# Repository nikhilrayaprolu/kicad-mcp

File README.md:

# kicad-mcp

**An MCP server that lets an AI agent design real, manufacturable PCBs.** The agent decides what a human electronics engineer decides: parts, connections, reference circuits, design rules, floorplan, and which parts must sit close to which pins. Deterministic engines turn that intent into a KiCad 10 project:

- a hierarchical schematic
- double-sided placement
- human-like routing with coupled differential pairs and length tuning
- copper pours
- DRC/ERC, Gerbers, BOM and pick-and-place

Everything runs headless.

It was built and evaluated by designing a **130-part Rockchip RV1106 Linux single-board computer from scratch** (`designs/rv1106-sbc/`):

- 4-layer, 65 × 50 mm
- USB-C, 10/100 Ethernet, SPI NAND, microSD, MIPI-CSI, 4 regulators
- **KiCad ERC 0 errors; DRC 0 errors, 0 warnings, 0 unconnected, 0 schematic-parity issues**
- every differential pair has equal via counts on both legs and is within its length tolerance (0.09–0.99 mm), using 45°-mitred serpentines
- `expert_review` quality gate: grade **expert**, 15/15 checks
- expert finishing: fiducials, labelled test points, edge via fence, legalised silkscreen

See [`docs/EVALUATION.md`](docs/EVALUATION.md).

| | |
|---|---|
| [`AGENTS.md`](AGENTS.md) | **Playbook for the AI agent**: the step-by-step flow, design rules and pitfalls that produce high-quality boards |
| [`docs/TOOLS.md`](docs/TOOLS.md) | Reference for all 28 MCP tools (generated from the server) |
| [`docs/ARCHITECTURE.md`](docs/ARCHITECTURE.md) | How it works: IR, placer, routers (own C++ router + Freerouting), verification |
| [`docs/EVALUATION.md`](docs/EVALUATION.md) | The RV1106 case study: metrics, iterations, bugs found, honest limitations |
| [`designs/rv1106-sbc/`](designs/rv1106-sbc) | Complete worked example: IR, KiCad files, every MCP call batch, fab outputs, renders |

## Gallery: the RV1106 example, generated end to end through the MCP tools

| PCB, top (3D) | PCB, bottom (3D): decoupling and crystal under the SoC |
|---|---|
|  |  |

| Layout: red F.Cu, olive In2.Cu, blue B.Cu; hatched = bottom-side parts | Length tuning: serpentine meanders on the CSI camera pairs |
|---|---|
|  |  |

| Copper pours on all 4 layers: F.Cu GND, In1 GND plane, In2 3V3/0V9/VSYS, B.Cu GND |
|---|
|  |

Generated hierarchical schematic, one sheet per functional block (ERC 0 errors, netlist identical to the design IR):

| SoC sheet: RV1106G3 symbol generated from the datasheet pin table | Power sheet: 4 bucks with E96 feedback dividers, USB-C sink, ESD |
|---|---|
|  |  |

| Ethernet sheet | Camera sheet | Root sheet |
|---|---|---|
|  |  |  |

<details><summary>v1 for comparison: single-sided, Freerouting only</summary>

| | |
|---|---|
|  |  |

</details>

---

## 1. Install (Linux x86_64, no sudo needed)

```bash
git clone git@github.com:nikhilrayaprolu/kicad-mcp.git
cd kicad-mcp
./scripts/install.sh
```

`install.sh` is idempotent and installs everything into the repo folder:

| Step | What |
|---|---|
| pixi env | Python 3.12, Java 25, `mcp`, numpy, scipy, shapely, pymupdf, … (installs pixi itself if missing) |
| KiCad 10.0.8 | `kicad-cli` and the stock symbol/footprint libraries, unpacked from the official KiCad PPA into `tools/kicad-root`, with the shared libraries it needs (tested on Ubuntu 24.04) |
| Freerouting 2.5 | `tools/freerouting/freerouting-2.5.0.jar` |
| hroute | builds the C++ router `router_cpp/hroute` (needs `g++`) |
| smoke test | `pixi run test`: 12 tests, including routed boards that must pass KiCad DRC |

If you already have **KiCad ≥ 9** (`kicad-cli` on PATH, libraries in `/usr/share/kicad`), run `SKIP_KICAD=1 ./scripts/install.sh`. On a non-Ubuntu distro, install KiCad from your package manager or Flatpak, then use `SKIP_KICAD=1`.

Hardware: any modern CPU works. Placement and routing portfolios scale with cores: 64 placement chains and 16–32 routing jobs run concurrently, about 0.4 GB RAM each. A 130-part board takes about 1–1.5 h end to end on 80 cores.

## 2. Connect it to your agent

**Claude Code:**

```bash
claude mcp add -s user kicad-mcp -- bash -c 'source /path/to/kicad-mcp/tools/env.sh && exec /path/to/kicad-mcp/.pixi/envs/default/bin/python -m llmpcb.server'
claude mcp list        # kicad-mcp: … ✔ Connected
```

**Any other MCP client** (Claude Desktop, Cursor, custom agents): it is a stdio server.

```json
{
  "mcpServers": {
    "kicad-mcp": {
      "command": "bash",
      "args": ["-c", "source /path/to/kicad-mcp/tools/env.sh && exec /path/to/kicad-mcp/.pixi/envs/default/bin/python -m llmpcb.server"]
    }
  }
}
```

Give the agent [`AGENTS.md`](AGENTS.md). In Claude Code, opening a session in this repo loads `CLAUDE.md` → `AGENTS.md`, and the `pcb-design` skill (`.claude/skills/pcb-design/`) is picked up automatically. With other agents, paste `AGENTS.md` into the system prompt or project instructions. The server also sends a condensed version as its MCP `instructions`.

**Scripted use, without an LLM client.** Run tool-call batches over real MCP stdio, which is how the example board was made:

```bash
pixi run python clients/mcp_call.py designs/myboard calls.json      # calls.json = [{"tool": ..., "args": {...}}, ...]
pixi run python clients/metrics.py designs/myboard                  # tool calls, latency, response sizes, DRC/ERC
```

## 3. How to ask for a board (for users)

The quality of the board depends mostly on the quality of your request. A good request contains:

1. **Function and interfaces:** "Linux SBC on RV1106G3 with USB-C power + USB2 device, 10/100 Ethernet (RJ45 with magnetics), SPI-NAND boot, microSD, 2-lane MIPI camera FPC, debug UART header, 2×10 GPIO header."
2. **Power:** input source and voltage, every rail with its voltage and estimated current, and sequencing if the chip needs it.
3. **Mechanics:** board size limit, connector edges, mounting holes, height limits, and whether **double-sided assembly** is allowed. That is recommended for fine-pitch SoCs: decoupling goes under the chip.
4. **Fab target:** e.g. JLCPCB 4-layer 1.6 mm (the default preset), and impedance targets for high-speed pairs.
5. **Sources:** datasheets and a reference-design schematic for every complex IC. The agent extracts pin tables into `knowledge/*.yaml` with page citations. Reference designs are the fastest way to correct support circuits.

Example prompt:

> Using the kicad-mcp server and AGENTS.md, design a 4-layer 50×40 mm ESP32-S3 board: USB-C 5 V in, 3.3 V/1 A buck, USB D+/D− to the S3 with ESD, 16 MB flash + 8 MB PSRAM (module), I2C header, 2 buttons, RGB LED, 4 M2 holes. Double-sided assembly allowed for passives. Target JLCPCB. Show me the placement render before routing, and stop only at DRC 0/0.

What you will see from the agent:

1. requirements and parts, then **schematic + ERC**
2. board setup, then **placement render**
3. **routing portfolio** (hybrid), then **DRC**
4. repair passes, then **length tuning**, then **design review**
5. **expert review**: the agent grades its own board, looks at the renders and fixes every failed check
6. **fab export + `publish`**: 3-D/2-D/per-layer/schematic images and a README gallery committed and pushed under `designs/<name>/`

You can intervene at any stage. For example: "move the USB connector to the bottom edge", "allow the crystal on the bottom side", "make VSYS 1 A", "route the camera pairs as coupled pairs".

Open the result in KiCad 10: `designs/<name>/<name>.kicad_pro`. The library tables in the project point at `llmpcb/library` for generated parts. After hand edits in KiCad, the agent can pull them back with `sync_from_kicad`.

### Quality checklist before ordering

- [ ] `expert_review` grade **expert**. It is the automated version of this list. It also checks:
  - copper pours on every layer
  - diff pairs with equal layer changes
  - 0 DRC warnings
  - stitching, fiducials, test points and labels
- [ ] `schematic_build`: ERC 0 errors, `netlist_parity.ok`
- [ ] `drc`: 0 errors, 0 unconnected, 0 parity; remaining warnings explained (pour islands, silkscreen)
- [ ] `design_review`: no errors; each `near`/`current`/`escape`/`diffpair` warning judged
- [ ] Generated footprints (`llmpcb/library`) checked against the manufacturer's land pattern
- [ ] I/O voltage domains, power sequencing and regulator choices reviewed by a human
- [ ] 3D renders (top and bottom) look right; connectors face the board edge

## 4. What is inside

| Layer | Implementation |
|---|---|
| Design IR | `design.json` (components, pin→net, netclasses, constraints, board) + `layout.json` (placement incl. side, tracks, vias, zones). KiCad files are regenerated from these. |
| Parts & knowledge | KiCad 10 stock libraries; curated parts with design facts; generated symbols/footprints from datasheet pin tables (`knowledge/*.yaml`) |
| Reference blocks | buck (E96 divider + sequencing RC), decoupling, crystal (CL→Cload), USB-C sink + ESD + pair, LED, button, … |
| Schematic | hierarchical sheets per block, labels at pin endpoints, PWR_FLAGs, ERC + netlist parity via `kicad-cli` |
| Placement | double-sided, rigid cluster macros, simulated annealing + legalisation + refinement, 64-seed parallel portfolio |
| Routing | **hroute** (own C++ router: 45°, negotiated congestion, neck-down, coupled diff pairs) + Freerouting; hybrid critical-first portfolio; DRC-scored parallel repair; serpentine length tuning |
| Verification | `kicad-cli` ERC/DRC (zones refilled, schematic parity), design review (decoupling distance, crystal, diff-pair skew and via symmetry, IPC-2221 current, escape feasibility), **`expert_review` quality gate** (pours on all layers, stitching, 45° routing, silkscreen, fiducials, test points, labels) |
| Copper | GND/power pours on every layer, saved filled; edge via fence + grid stitching; floating islands stitched to the plane (`stitch_islands`) |
| Publishing | `publish`: renders + gallery README per board, git commit/push of only that board's files |
| Output | Gerber X2, Excellon, CPL, JLC BOM, IPC-D-356, PDFs, 3D renders |

Why it writes KiCad files directly instead of using `pcbnew`/IPC: KiCad 10's IPC API needs a running GUI, and the SWIG `pcbnew` module is deprecated. kicad-cli is used as the verifier, and the writers are checked against KiCad itself. See `docs/ARCHITECTURE.md`. An optional `ipc_sync` tool pushes to or pulls from a running KiCad GUI.

## 5. Development

```bash
source tools/env.sh
pixi run test                                   # unit + end-to-end (route -> KiCad DRC clean)
pixi run python clients/gen_tool_docs.py        # regenerate docs/TOOLS.md after changing tools
g++ -O3 -march=native -std=c++17 -o router_cpp/hroute router_cpp/hroute.cpp
```

Router debugging (`router_cpp/hroute.cpp`, problem files in `designs/<x>/out/hroute/*/problem.txt`):

| Variable | Effect |
|---|---|
| `HROUTE_PROBE="net layer x y"` | ASCII legality map around a point |
| `HROUTE_DBG=1` | failed-search statistics and flood-fill reachability |
| `HROUTE_BUDGET` | negotiation time budget, in seconds |
| `HROUTE_CAP` | A* expansion cap |
| `HROUTE_SEQ=1` | legacy sequential rip-up |

## Limitations (honest)

- **hroute's completion:** it completes 75–80 of 84 nets on the dense RV1106 board; Freerouting finishes the rest in hybrid mode. Its strength is critical nets and coupled pairs.
- **Coupled pairs** survive only where the placement leaves a corridor. Others are routed single-ended and then length-tuned.
- **Generated footprints** (e.g. the QFN-128) are derived from datasheet drawings and must be verified.
- **Not covered:** high-speed DDR fan-out, impedance field solving, SI/PI/thermal simulation.
- **IPC live mode** is implemented but untested, since there was no KiCad GUI in the development environment.

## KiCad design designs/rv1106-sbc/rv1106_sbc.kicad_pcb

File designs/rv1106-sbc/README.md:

# LP-1106 RV1106 SBC (rev A)

LP-1106: Linux SBC on Rockchip RV1106G3 (Cortex-A7, 1 TOPS NPU, 256MB DDR3L in package). USB-C power+OTG, 10/100 Ethernet, SPI NAND boot, microSD, 2-lane MIPI CSI, debug UART, 2x10 GPIO.

65.0 × 50.0 mm, 4 layers, 137 parts, 374 vias. Generated with kicad-mcp.

| Check | Result |
|---|---|
| Expert review | **expert** (15 passed, 0 failed) |
| KiCad DRC | 0 errors, 0 warnings, 0 unconnected, 0 parity |
| Pour coverage | B.Cu 74%, F.Cu 57%, In1.Cu 83%, In2.Cu 62% |

| Top (3D) | Bottom (3D) |
|---|---|
|  |  |

| layer_F_Cu.png | layer_In1_Cu.png | layer_In2_Cu.png | layer_B_Cu.png |
|---|---|---|---|
|  |  |  |  |

## Schematic

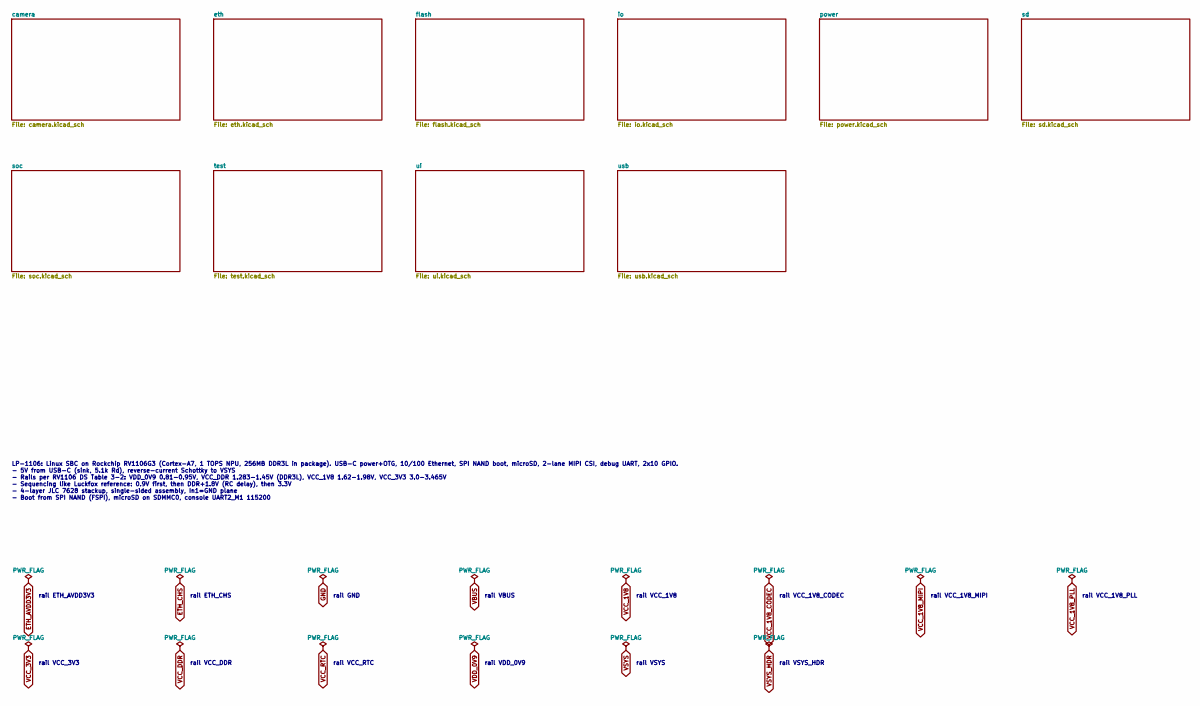
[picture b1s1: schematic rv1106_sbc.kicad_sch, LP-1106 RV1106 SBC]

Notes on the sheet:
rail ETH_AVDD3V3
rail ETH_CHS
rail GND
rail VBUS
rail VCC_1V8
rail VCC_1V8_CODEC
rail VCC_1V8_MIPI
rail VCC_1V8_PLL
rail VCC_3V3
rail VCC_DDR
rail VCC_RTC
rail VDD_0V9
rail VSYS
rail VSYS_HDR
LP-1106: Linux SBC on Rockchip RV1106G3 (Cortex-A7, 1 TOPS NPU, 256MB DDR3L in package). USB-C power+OTG, 10/100 Ethernet, SPI NAND boot, microSD, 2-lane MIPI CSI, debug UART, 2x10 GPIO. - 5V from USB-C (sink, 5.1k Rd), reverse-current Schottky to VSYS - Rails per RV1106 DS Table 3-2: VDD_0V9 0.81-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

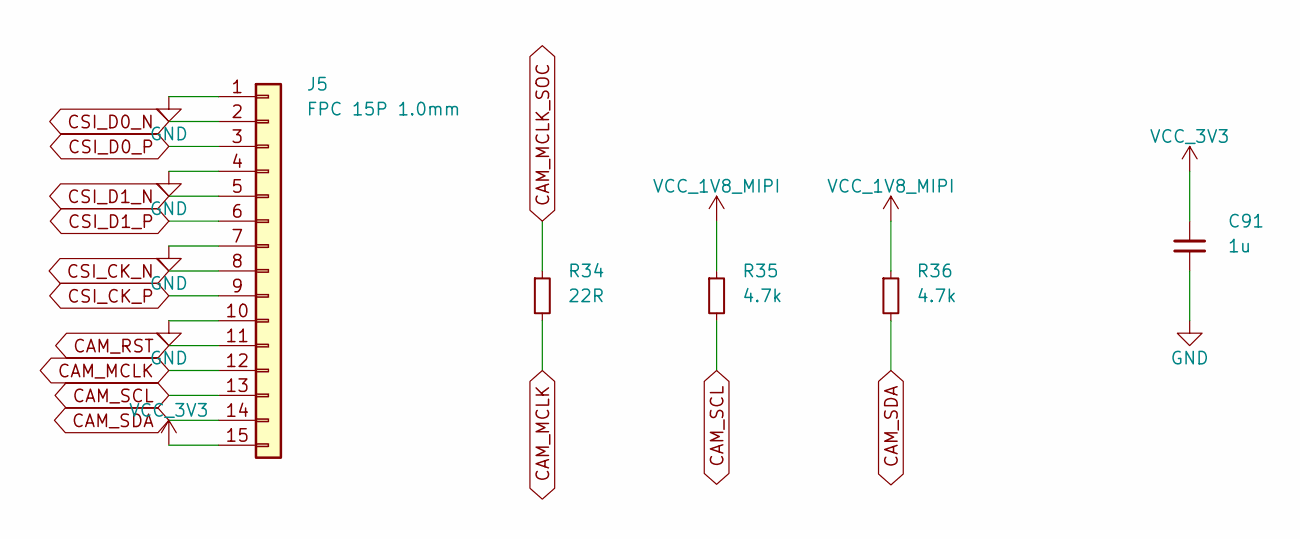
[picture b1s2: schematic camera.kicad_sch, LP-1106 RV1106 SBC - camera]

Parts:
C91: 1u; C_0402_1005Metric
J5: FPC 15P 1.0mm; Molex_200528-0150_1x15-1MP_P1.00mm_Horizontal
R34: 22R; R_0402_1005Metric
R35, R36: 4.7k; R_0402_1005Metric

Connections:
CAM_MCLK: J5.12, R34.2
CAM_MCLK_SOC: R34.1; also elsewhere on the board
CAM_RST: J5.11; also elsewhere on the board
CAM_SCL: J5.13, R35.2; also elsewhere on the board
CAM_SDA: J5.14, R36.2; also elsewhere on the board
CSI_CK_N: J5.8; also elsewhere on the board
CSI_CK_P: J5.9; also elsewhere on the board
CSI_D0_N: J5.2; also elsewhere on the board
CSI_D0_P: J5.3; also elsewhere on the board
CSI_D1_N: J5.5; also elsewhere on the board
CSI_D1_P: J5.6; also elsewhere on the board
GND: C91.2, J5.1, J5.4, J5.7, J5.10; also elsewhere on the board
VCC_1V8_MIPI: R35.1, R36.1; also elsewhere on the board
VCC_3V3: C91.1, J5.15; also elsewhere on the board

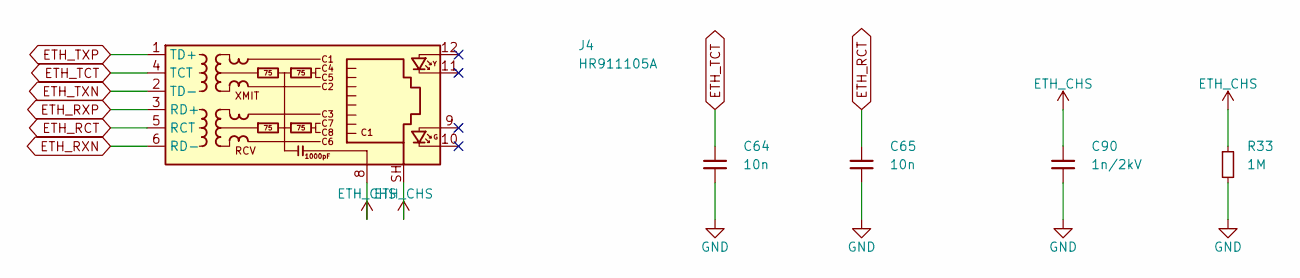
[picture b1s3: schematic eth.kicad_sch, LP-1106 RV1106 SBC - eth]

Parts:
C64, C65: 10n; C_0402_1005Metric
C90: 1n/2kV; C_1206_3216Metric
J4: HR911105A; RJ45_Hanrun_HR911105A_Horizontal; MPN HR911105A; LCSC C12074
R33: 1M; R_0603_1608Metric

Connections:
ETH_CHS: C90.1, J4.8, J4.SH, R33.1
ETH_RCT: C65.1, J4.5 (RCT)
ETH_RXN: J4.6 (RD-); also elsewhere on the board
ETH_RXP: J4.3 (RD+); also elsewhere on the board
ETH_TCT: C64.1, J4.4 (TCT)
ETH_TXN: J4.2 (TD-); also elsewhere on the board
ETH_TXP: J4.1 (TD+); also elsewhere on the board
GND: C64.2, C65.2, C90.2, R33.2; also elsewhere on the board

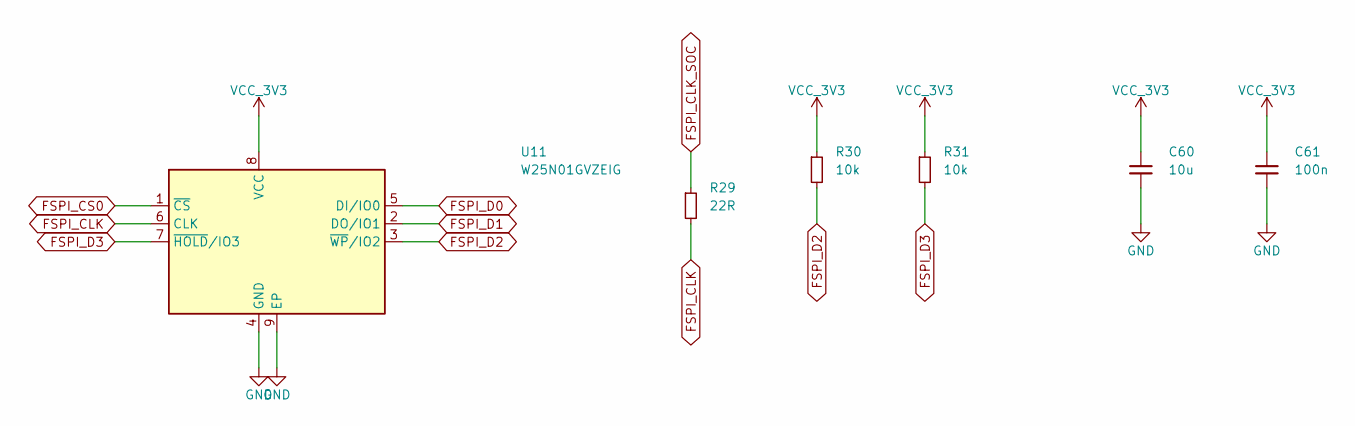
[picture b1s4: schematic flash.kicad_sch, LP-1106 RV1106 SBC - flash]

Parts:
C60: 10u; C_0603_1608Metric
C61: 100n; C_0402_1005Metric
R29: 22R; R_0402_1005Metric
R30, R31: 10k; R_0402_1005Metric
U11: W25N01GVZEIG; WSON-8-1EP_8x6mm_P1.27mm_EP3.4x4.3mm; MPN W25N01GVZEIG; LCSC C111706

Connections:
FSPI_CLK: R29.2, U11.6 (CLK)
FSPI_CLK_SOC: R29.1; also elsewhere on the board
FSPI_CS0: U11.1 (~CS); also elsewhere on the board
FSPI_D0: U11.5 (DI/IO0); also elsewhere on the board
FSPI_D1: U11.2 (DO/IO1); also elsewhere on the board
FSPI_D2: R30.2, U11.3 (~WP/IO2); also elsewhere on the board
FSPI_D3: R31.2, U11.7 (~HOLD/IO3); also elsewhere on the board
GND: C60.2, C61.2, U11.4 (GND), U11.9 (EP); also elsewhere on the board
VCC_3V3: C60.1, C61.1, R30.1, R31.1, U11.8 (VCC); also elsewhere on the board

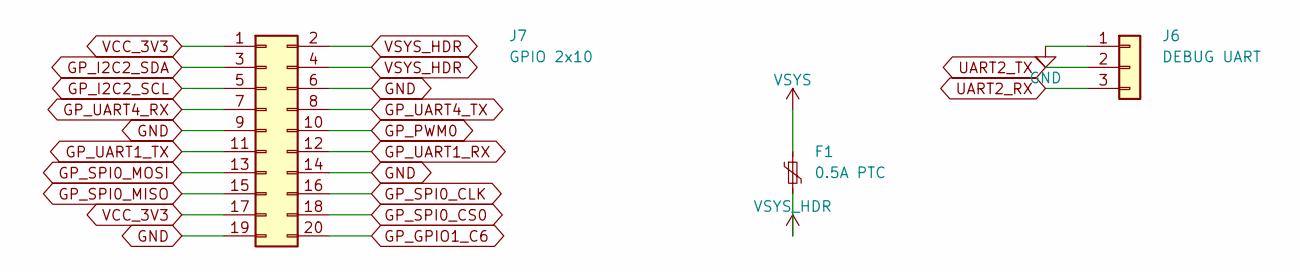
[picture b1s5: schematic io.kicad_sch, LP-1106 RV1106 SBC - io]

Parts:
F1: 0.5A PTC; Fuse_1206_3216Metric; MPN SMD1206P050TF
J6: DEBUG UART; PinHeader_1x03_P2.54mm_Vertical
J7: GPIO 2x10; PinHeader_2x10_P2.54mm_Vertical

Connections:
GND: J6.1, J7.6, J7.9, J7.14, J7.19; also elsewhere on the board
GP_GPIO1_C6: J7.20; also elsewhere on the board
GP_I2C2_SCL: J7.5; also elsewhere on the board
GP_I2C2_SDA: J7.3; also elsewhere on the board
GP_PWM0: J7.10; also elsewhere on the board
GP_SPI0_CLK: J7.16; also elsewhere on the board
GP_SPI0_CS0: J7.18; also elsewhere on the board
GP_SPI0_MISO: J7.15; also elsewhere on the board
GP_SPI0_MOSI: J7.13; also elsewhere on the board
GP_UART1_RX: J7.12; also elsewhere on the board
GP_UART1_TX: J7.11; also elsewhere on the board
GP_UART4_RX: J7.7; also elsewhere on the board
GP_UART4_TX: J7.8; also elsewhere on the board
UART2_RX: J6.3; also elsewhere on the board
UART2_TX: J6.2; also elsewhere on the board
VCC_3V3: J7.1, J7.17; also elsewhere on the board
VSYS: F1.1; also elsewhere on the board
VSYS_HDR: F1.2, J7.2, J7.4

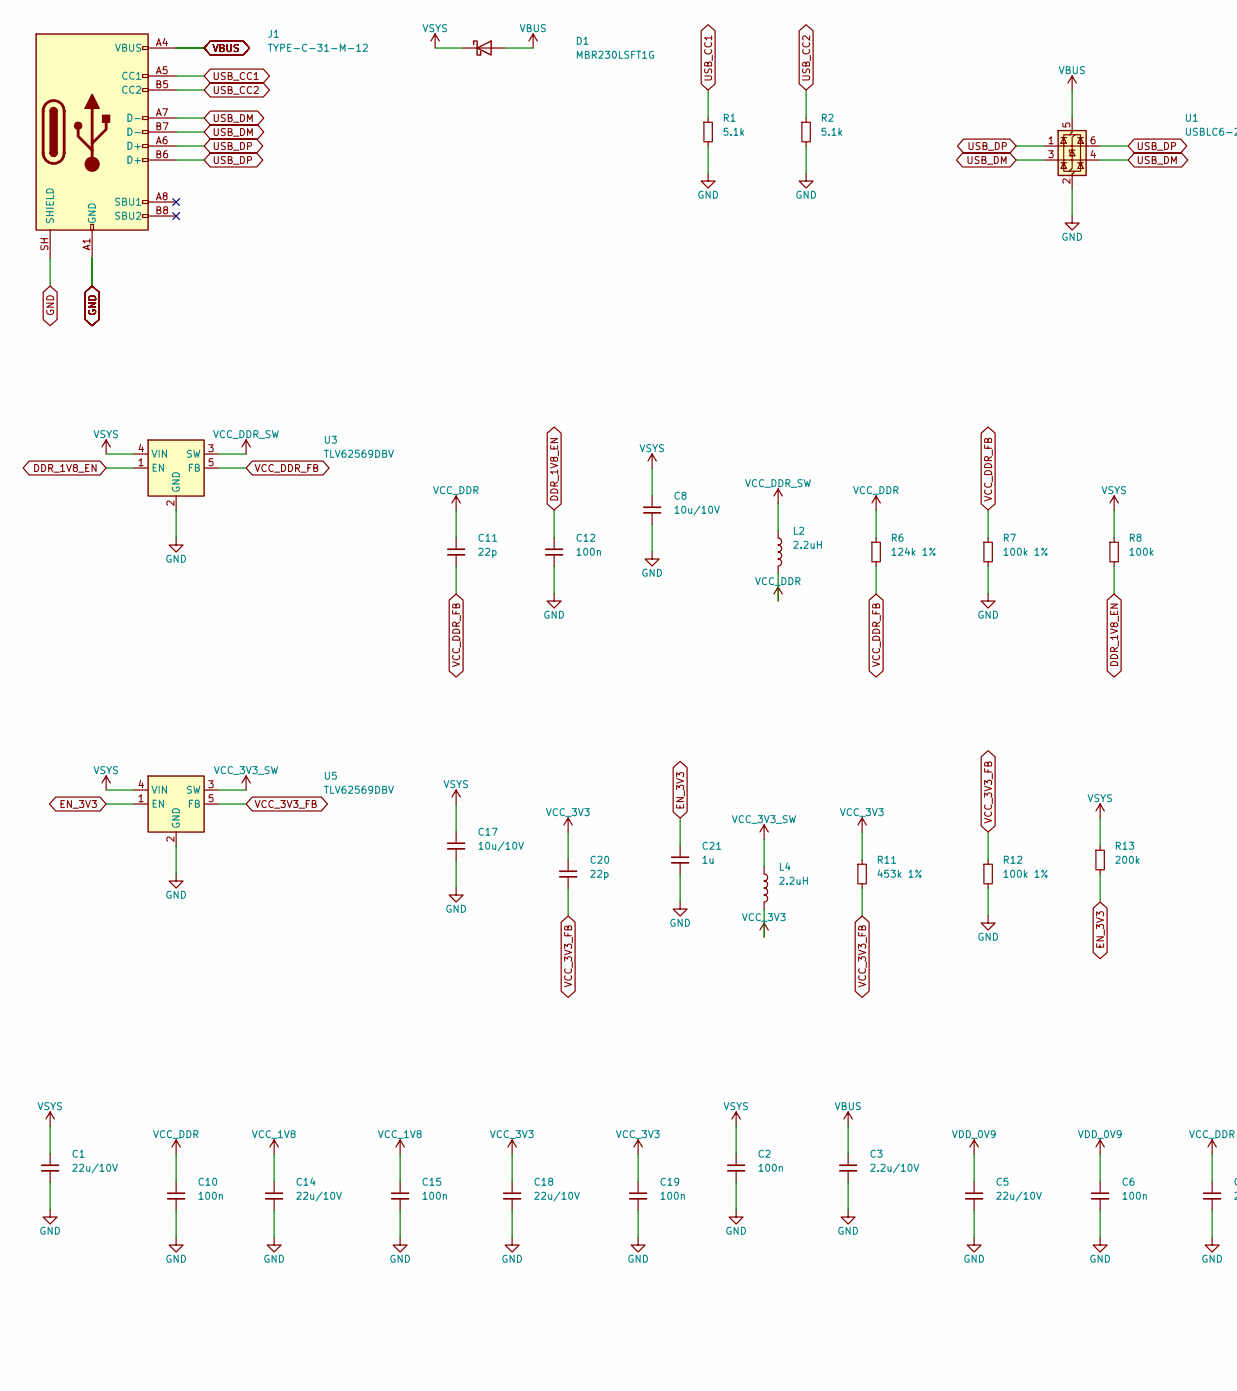
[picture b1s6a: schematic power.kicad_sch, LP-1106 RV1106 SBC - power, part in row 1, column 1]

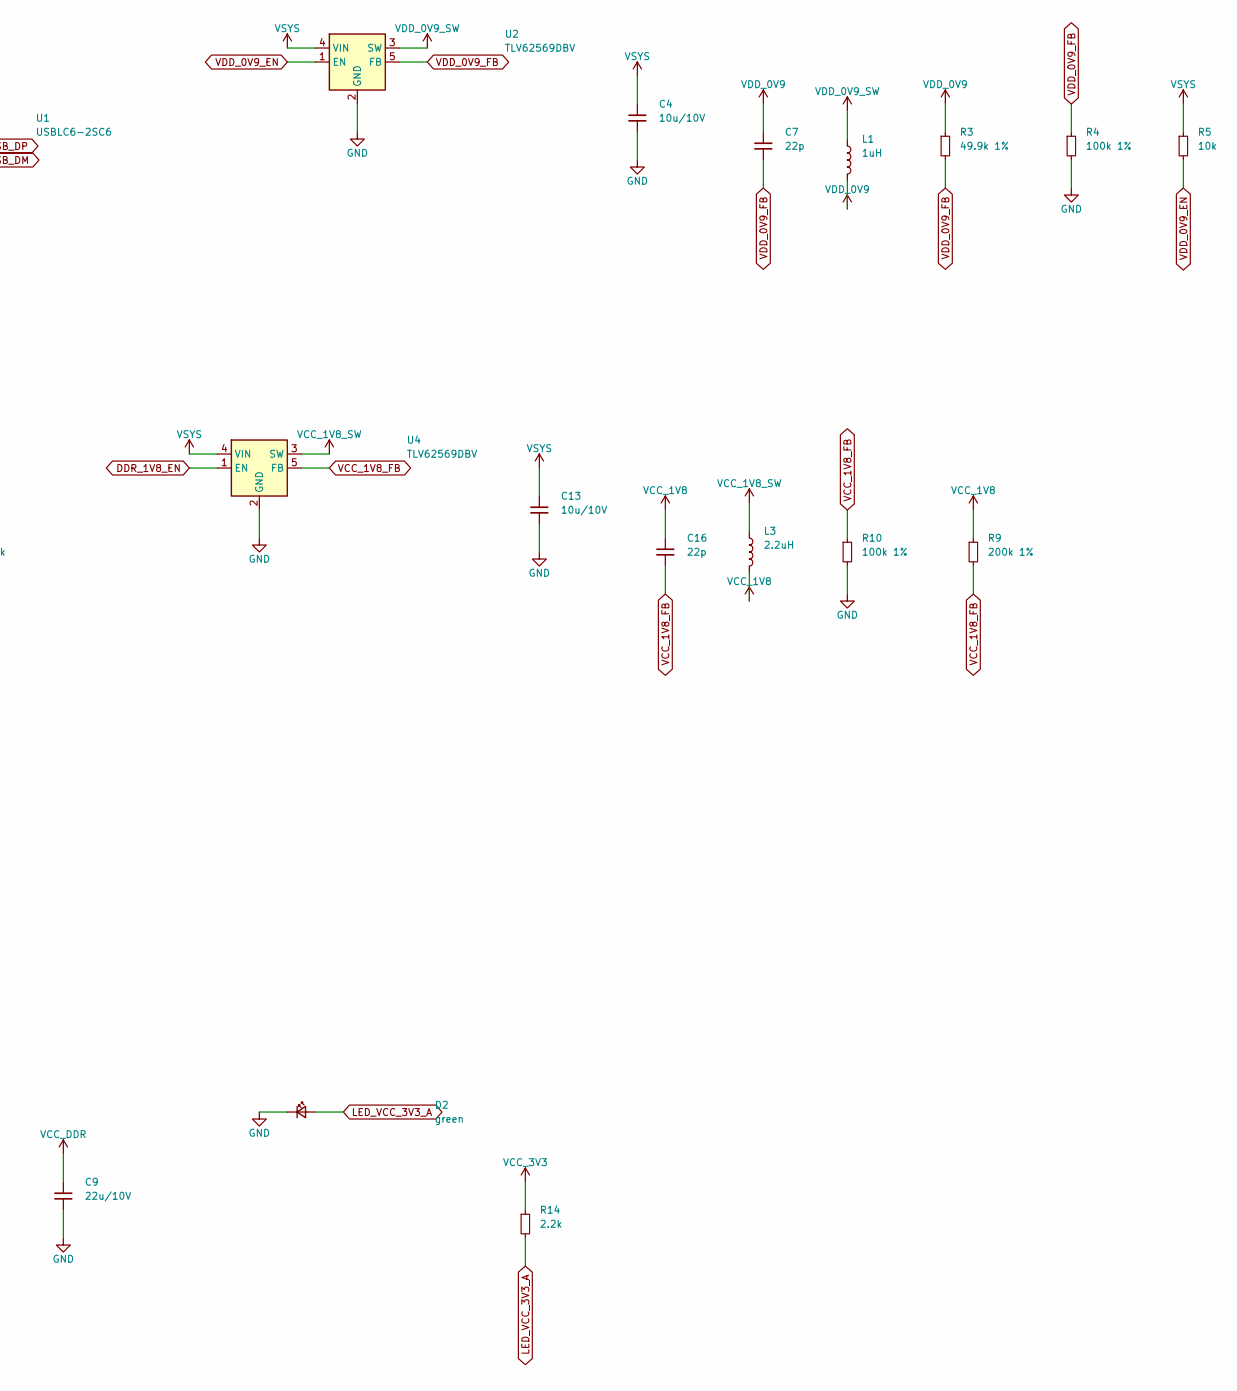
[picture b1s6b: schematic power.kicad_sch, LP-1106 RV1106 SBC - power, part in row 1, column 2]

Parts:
C1, C5, C9, C14, C18: 22u/10V; C_0805_2012Metric
C2, C6, C10, C12, C15, C19: 100n; C_0402_1005Metric
C3: 2.2u/10V; C_0603_1608Metric
C4, C8, C13, C17: 10u/10V; C_0603_1608Metric
C7, C11, C16, C20: 22p; C_0402_1005Metric
C21: 1u; C_0402_1005Metric
D1: MBR230LSFT1G; D_SOD-123F; MPN MBR230LSFT1G
D2: green; LED_0603_1608Metric
J1: TYPE-C-31-M-12; USB_C_Receptacle_HRO_TYPE-C-31-M-12; MPN TYPE-C-31-M-12; LCSC C165948
L1: 1uH; L_Cenker_CKCS252012; MPN CKCS252012
L2, L3, L4: 2.2uH; L_Cenker_CKCS252012; MPN CKCS252012
R1, R2: 5.1k; R_0402_1005Metric
R3: 49.9k 1%; R_0402_1005Metric
R4, R7, R10, R12: 100k 1%; R_0402_1005Metric
R5: 10k; R_0402_1005Metric
R6: 124k 1%; R_0402_1005Metric
R8: 100k; R_0402_1005Metric
R9: 200k 1%; R_0402_1005Metric
R11: 453k 1%; R_0402_1005Metric
R13: 200k; R_0402_1005Metric
R14: 2.2k; R_0402_1005Metric
U1: USBLC6-2SC6; SOT-23-6; MPN USBLC6-2SC6; LCSC C7519
U2, U3, U4, U5: TLV62569DBV; SOT-23-5; MPN TLV62569DBVR; LCSC C141836

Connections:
DDR_1V8_EN: C12.1, R8.2, U3.1 (EN), U4.1 (EN)
EN_3V3: C21.1, R13.2, U5.1 (EN)
GND: C1.2, C2.2, C3.2, C4.2, C5.2, C6.2, C8.2, C9.2, C10.2, C12.2, C13.2, C14.2, C15.2, C17.2, C18.2, C19.2, C21.2, D2.1 (K), J1.A1 (GND), J1.A12 (GND), J1.B1 (GND), J1.B12 (GND), J1.SH (SHIELD), R1.2, R2.2, R4.2, R7.2, R10.2, R12.2, U1.2 (GND), U2.2 (GND), U3.2 (GND), U4.2 (GND), U5.2 (GND); also elsewhere on the board
LED_VCC_3V3_A: D2.2 (A), R14.2
USB_CC1: J1.A5 (CC1), R1.1
USB_CC2: J1.B5 (CC2), R2.1
USB_DM: J1.A7 (D-), J1.B7 (D-), U1.3 (I/O2), U1.4 (I/O2); also elsewhere on the board
USB_DP: J1.A6 (D+), J1.B6 (D+), U1.1 (I/O1), U1.6 (I/O1); also elsewhere on the board
VBUS: C3.1, D1.2 (A), J1.A4 (VBUS), J1.A9 (VBUS), J1.B4 (VBUS), J1.B9 (VBUS), U1.5 (VBUS); also elsewhere on the board
VCC_1V8: C14.1, C15.1, C16.1, L3.2, R9.1; also elsewhere on the board
VCC_1V8_FB: C16.2, R9.2, R10.1, U4.5 (FB)
VCC_1V8_SW: L3.1, U4.3 (SW)
VCC_3V3: C18.1, C19.1, C20.1, L4.2, R11.1, R14.1; also elsewhere on the board
VCC_3V3_FB: C20.2, R11.2, R12.1, U5.5 (FB)
VCC_3V3_SW: L4.1, U5.3 (SW)
VCC_DDR: C9.1, C10.1, C11.1, L2.2, R6.1; also elsewhere on the board
VCC_DDR_FB: C11.2, R6.2, R7.1, U3.5 (FB)
VCC_DDR_SW: L2.1, U3.3 (SW)
VDD_0V9: C5.1, C6.1, C7.1, L1.2, R3.1; also elsewhere on the board
VDD_0V9_EN: R5.2, U2.1 (EN)
VDD_0V9_FB: C7.2, R3.2, R4.1, U2.5 (FB)
VDD_0V9_SW: L1.1, U2.3 (SW)
VSYS: C1.1, C2.1, C4.1, C8.1, C13.1, C17.1, D1.1 (K), R5.1, R8.1, R13.1, U2.4 (VIN), U3.4 (VIN), U4.4 (VIN), U5.4 (VIN); also elsewhere on the board

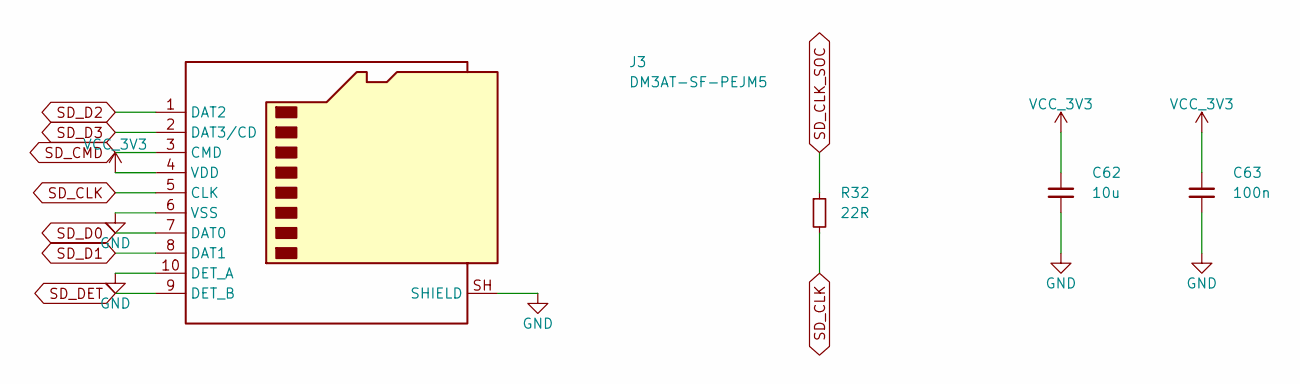
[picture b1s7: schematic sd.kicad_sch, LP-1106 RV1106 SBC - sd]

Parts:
C62: 10u; C_0603_1608Metric
C63: 100n; C_0402_1005Metric
J3: DM3AT-SF-PEJM5; microSD_HC_Hirose_DM3AT-SF-PEJM5; MPN DM3AT-SF-PEJM5
R32: 22R; R_0402_1005Metric

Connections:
GND: C62.2, C63.2, J3.6 (VSS), J3.10 (DET_A), J3.SH (SHIELD); also elsewhere on the board
SD_CLK: J3.5 (CLK), R32.2
SD_CLK_SOC: R32.1; also elsewhere on the board
SD_CMD: J3.3 (CMD); also elsewhere on the board
SD_D0: J3.7 (DAT0); also elsewhere on the board
SD_D1: J3.8 (DAT1); also elsewhere on the board
SD_D2: J3.1 (DAT2); also elsewhere on the board
SD_D3: J3.2 (DAT3/CD); also elsewhere on the board
SD_DET: J3.9 (DET_B); also elsewhere on the board
VCC_3V3: C62.1, C63.1, J3.4 (VDD); also elsewhere on the board

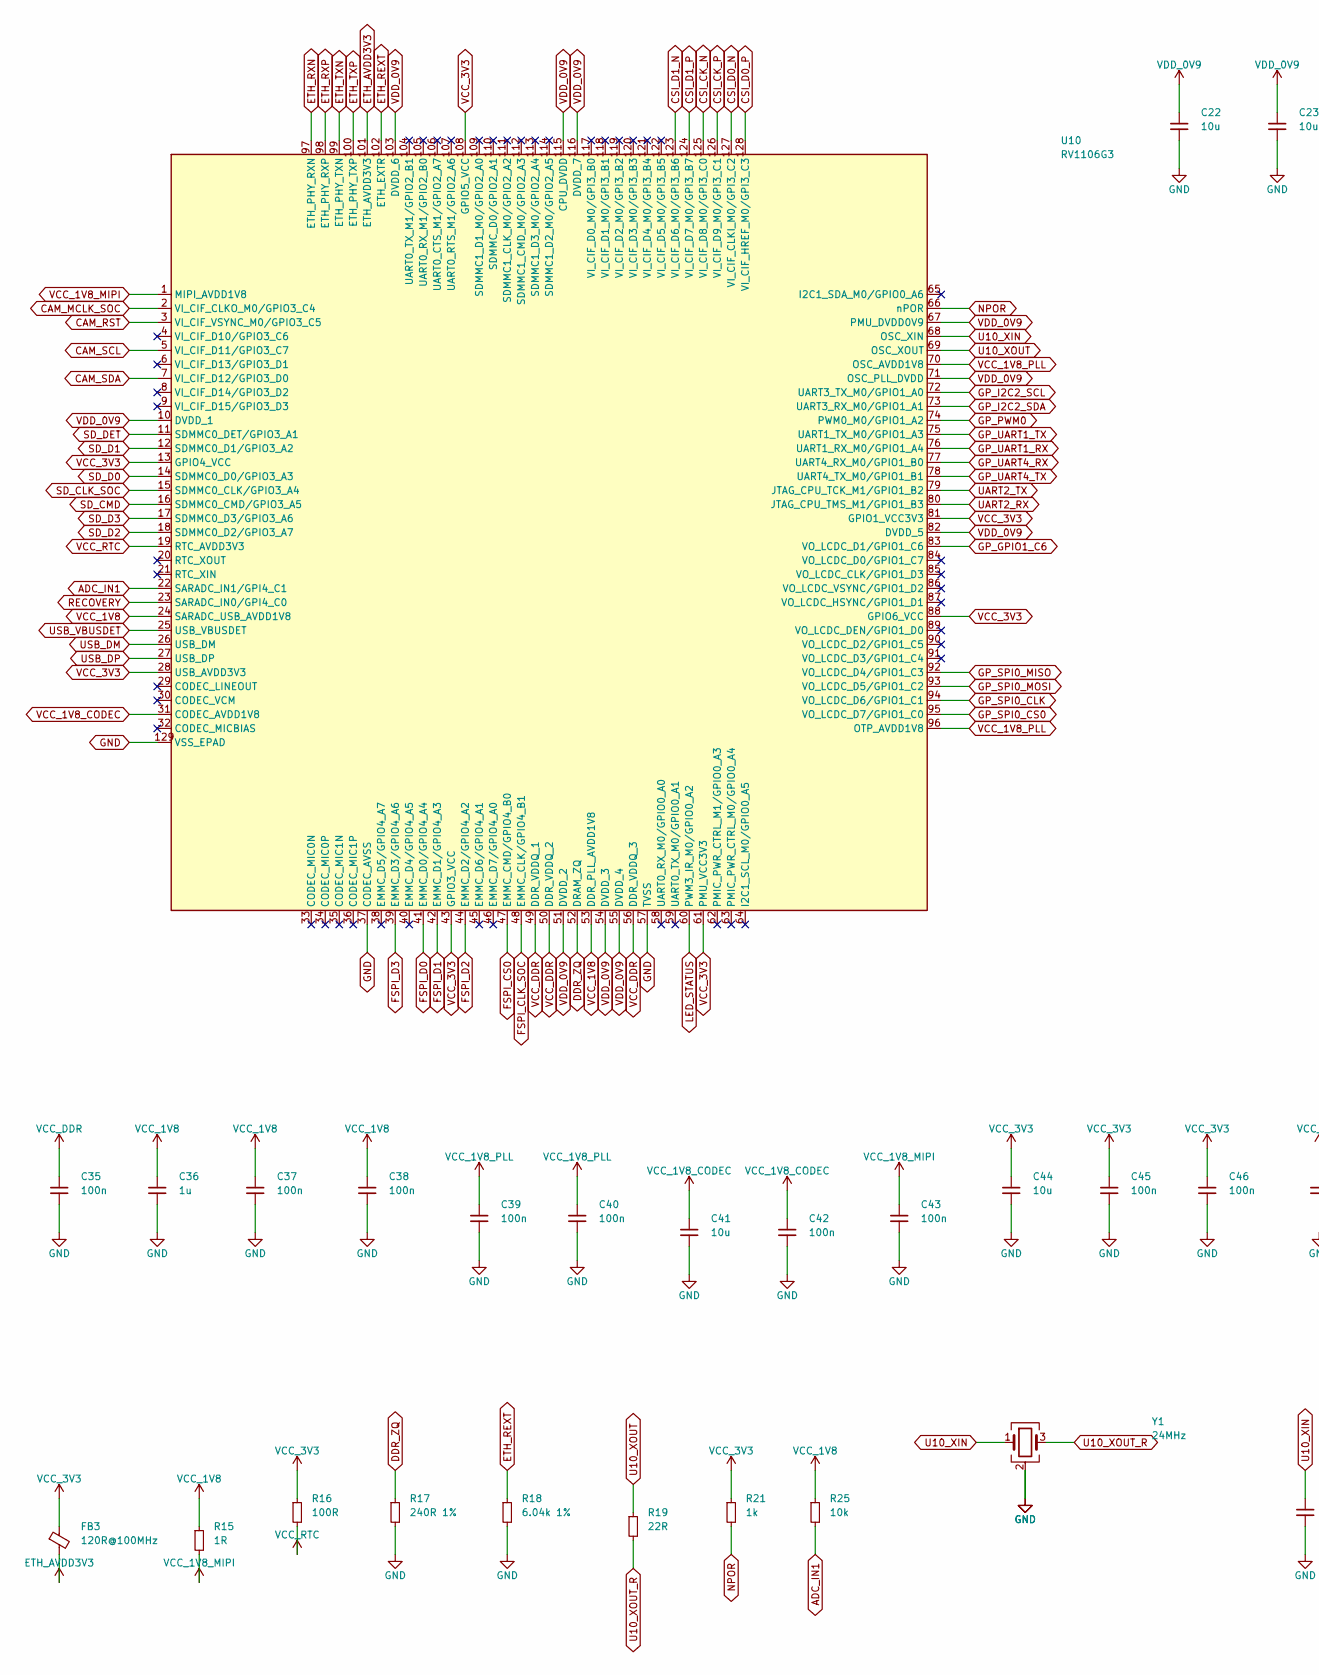
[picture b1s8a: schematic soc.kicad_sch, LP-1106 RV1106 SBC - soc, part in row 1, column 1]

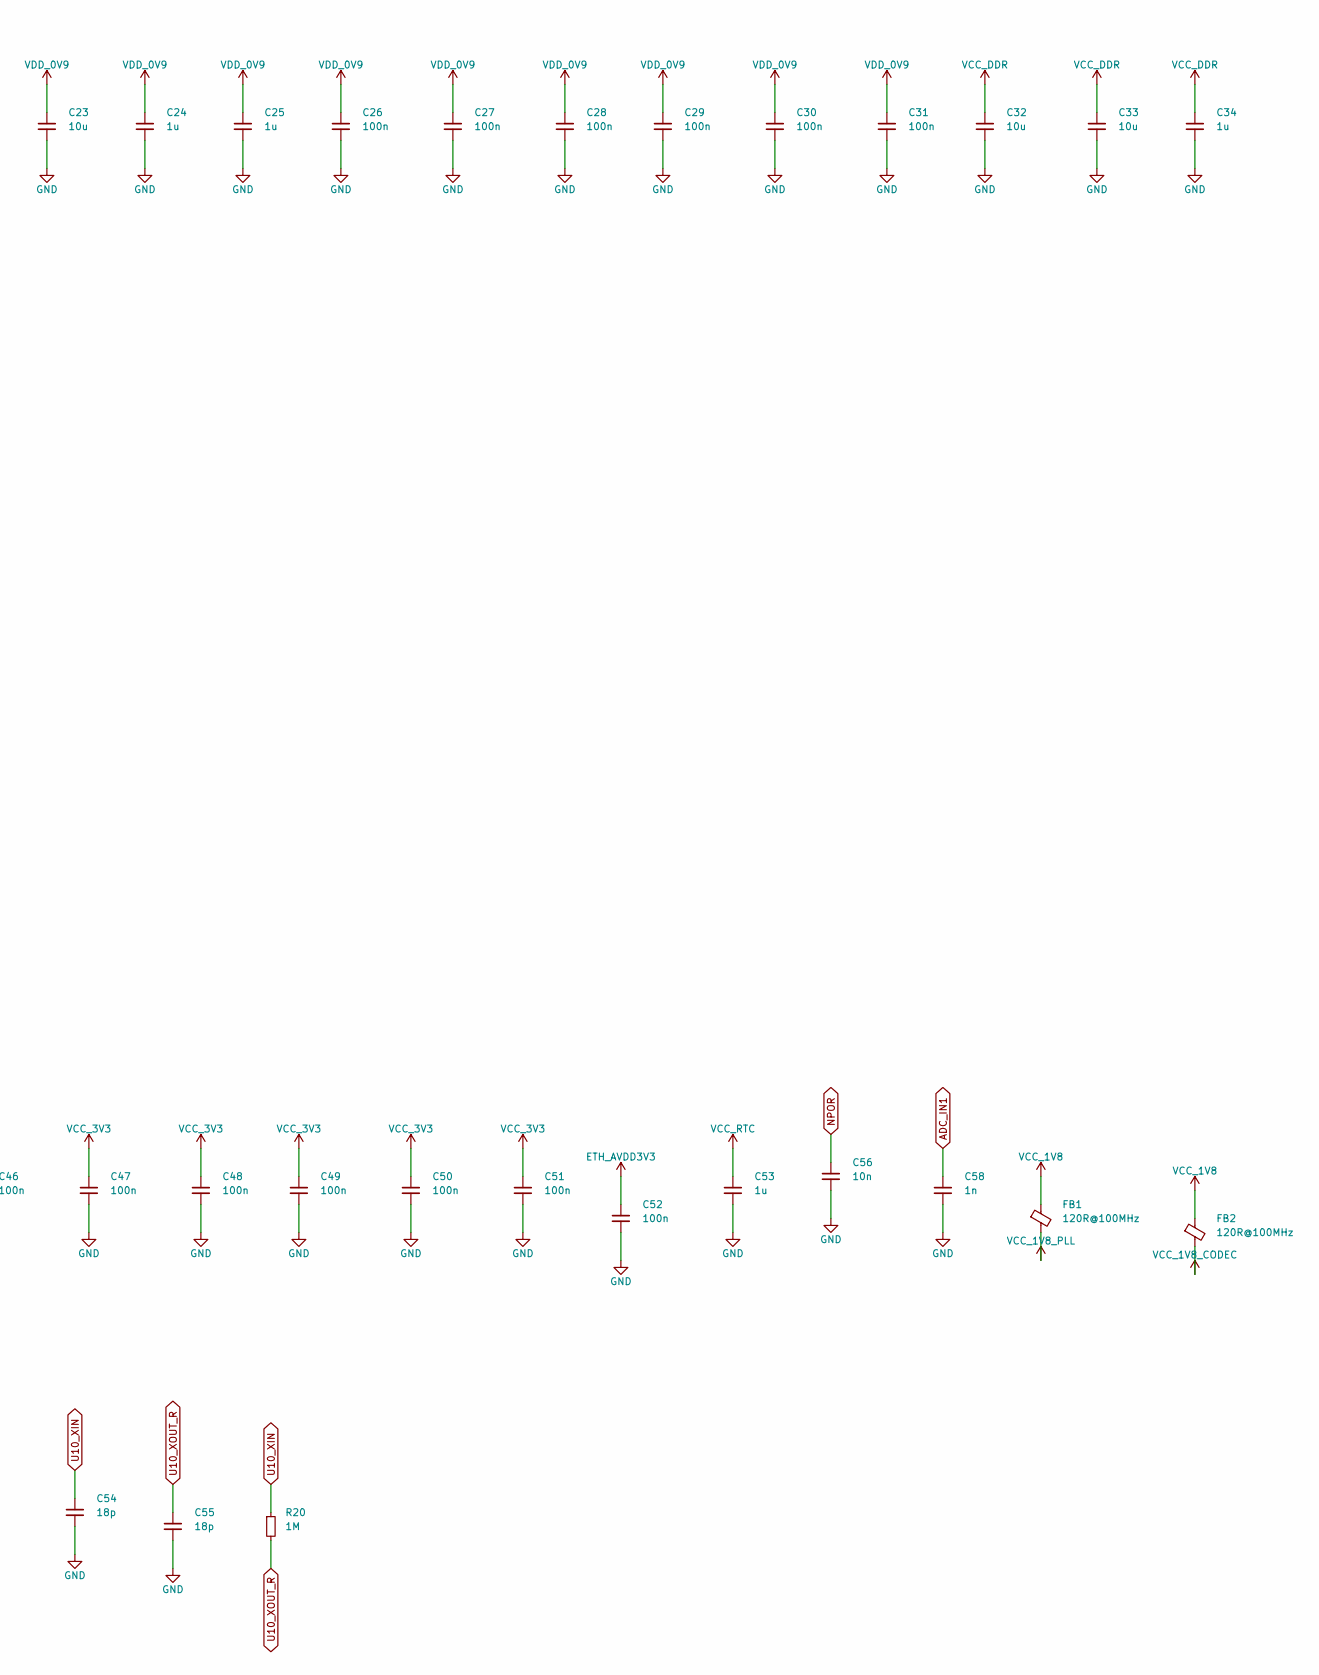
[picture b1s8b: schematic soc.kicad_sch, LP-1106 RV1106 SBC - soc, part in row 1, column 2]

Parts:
C22, C23, C32, C33, C41, C44: 10u; C_0603_1608Metric
C24, C25, C34, C36, C53: 1u; C_0402_1005Metric
C26, C27, C28, C29, C30, C31, C35, C37, C38, C39, C40, C42, C43, C45, C46, C47, C48, C49, C50, C51, C52: 100n; C_0402_1005Metric
C54, C55: 18p; C_0402_1005Metric
C56: 10n; C_0402_1005Metric
C58: 1n; C_0402_1005Metric
FB1, FB2, FB3: 120R@100MHz; L_0402_1005Metric; MPN BLM15PD121SN1D
R15: 1R; R_0402_1005Metric
R16: 100R; R_0402_1005Metric
R17: 240R 1%; R_0402_1005Metric
R18: 6.04k 1%; R_0402_1005Metric
R19: 22R; R_0402_1005Metric
R20: 1M; R_0402_1005Metric
R21: 1k; R_0402_1005Metric
R25: 10k; R_0402_1005Metric
U10: RV1106G3; QFN-128-1EP_12.3x12.3mm_P0.35mm_EP7x7mm; MPN RV1106G3
Y1: 24MHz; Crystal_SMD_3225-4Pin_3.2x2.5mm

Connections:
ADC_IN1: C58.1, R25.2, U10.22 (SARADC_IN1/GPI4_C1)
CAM_MCLK_SOC: U10.2 (VI_CIF_CLKO_M0/GPIO3_C4); also elsewhere on the board
CAM_RST: U10.3 (VI_CIF_VSYNC_M0/GPIO3_C5); also elsewhere on the board
CAM_SCL: U10.5 (VI_CIF_D11/GPIO3_C7); also elsewhere on the board
CAM_SDA: U10.7 (VI_CIF_D12/GPIO3_D0); also elsewhere on the board
CSI_CK_N: U10.125 (VI_CIF_D8_M0/GPI3_C0); also elsewhere on the board
CSI_CK_P: U10.126 (VI_CIF_D9_M0/GPI3_C1); also elsewhere on the board
CSI_D0_N: U10.127 (VI_CIF_CLKI_M0/GPI3_C2); also elsewhere on the board
CSI_D0_P: U10.128 (VI_CIF_HREF_M0/GPI3_C3); also elsewhere on the board
CSI_D1_N: U10.123 (VI_CIF_D6_M0/GPI3_B6); also elsewhere on the board
CSI_D1_P: U10.124 (VI_CIF_D7_M0/GPI3_B7); also elsewhere on the board
DDR_ZQ: R17.1, U10.52 (DRAM_ZQ)
ETH_AVDD3V3: C52.1, FB3.2, U10.101 (ETH_AVDD3V3)
ETH_REXT: R18.1, U10.102 (ETH_EXTR)
ETH_RXN: U10.97 (ETH_PHY_RXN); also elsewhere on the board
ETH_RXP: U10.98 (ETH_PHY_RXP); also elsewhere on the board
ETH_TXN: U10.99 (ETH_PHY_TXN); also elsewhere on the board
ETH_TXP: U10.100 (ETH_PHY_TXP); also elsewhere on the board
FSPI_CLK_SOC: U10.48 (EMMC_CLK/GPIO4_B1); also elsewhere on the board
FSPI_CS0: U10.47 (EMMC_CMD/GPIO4_B0); also elsewhere on the board
FSPI_D0: U10.41 (EMMC_D0/GPIO4_A4); also elsewhere on the board
FSPI_D1: U10.42 (EMMC_D1/GPIO4_A3); also elsewhere on the board
FSPI_D2: U10.44 (EMMC_D2/GPIO4_A2); also elsewhere on the board
FSPI_D3: U10.39 (EMMC_D3/GPIO4_A6); also elsewhere on the board
GND: C22.2, C23.2, C24.2, C25.2, C26.2, C27.2, C28.2, C29.2, C30.2, C31.2, C32.2, C33.2, C34.2, C35.2, C36.2, C37.2, C38.2, C39.2, C40.2, C41.2, C42.2, C43.2, C44.2, C45.2, C46.2, C47.2, C48.2, C49.2, C50.2, C51.2, C52.2, C53.2, C54.2, C55.2, C56.2, C58.2, R17.2, R18.2, U10.37 (CODEC_AVSS), U10.57 (TVSS), U10.129 (VSS_EPAD), Y1.2 (G), Y1.4 (G); also elsewhere on the board
GP_GPIO1_C6: U10.83 (VO_LCDC_D1/GPIO1_C6); also elsewhere on the board
GP_I2C2_SCL: U10.72 (UART3_TX_M0/GPIO1_A0); also elsewhere on the board
GP_I2C2_SDA: U10.73 (UART3_RX_M0/GPIO1_A1); also elsewhere on the board
GP_PWM0: U10.74 (PWM0_M0/GPIO1_A2); also elsewhere on the board
GP_SPI0_CLK: U10.94 (VO_LCDC_D6/GPIO1_C1); also elsewhere on the board
GP_SPI0_CS0: U10.95 (VO_LCDC_D7/GPIO1_C0); also elsewhere on the board
GP_SPI0_MISO: U10.92 (VO_LCDC_D4/GPIO1_C3); also elsewhere on the board
GP_SPI0_MOSI: U10.93 (VO_LCDC_D5/GPIO1_C2); also elsewhere on the board
GP_UART1_RX: U10.76 (UART1_RX_M0/GPIO1_A4); also elsewhere on the board
GP_UART1_TX: U10.75 (UART1_TX_M0/GPIO1_A3); also elsewhere on the board
GP_UART4_RX: U10.77 (UART4_RX_M0/GPIO1_B0); also elsewhere on the board
GP_UART4_TX: U10.78 (UART4_TX_M0/GPIO1_B1); also elsewhere on the board
LED_STATUS: U10.60 (PWM3_IR_M0/GPIO0_A2); also elsewhere on the board
NPOR: C56.1, R21.2, U10.66 (nPOR); also elsewhere on the board
RECOVERY: U10.23 (SARADC_IN0/GPI4_C0); also elsewhere on the board
SD_CLK_SOC: U10.15 (SDMMC0_CLK/GPIO3_A4); also elsewhere on the board
SD_CMD: U10.16 (SDMMC0_CMD/GPIO3_A5); also elsewhere on the board
SD_D0: U10.14 (SDMMC0_D0/GPIO3_A3); also elsewhere on the board
SD_D1: U10.12 (SDMMC0_D1/GPIO3_A2); also elsewhere on the board
SD_D2: U10.18 (SDMMC0_D2/GPIO3_A7); also elsewhere on the board
SD_D3: U10.17 (SDMMC0_D3/GPIO3_A6); also elsewhere on the board
SD_DET: U10.11 (SDMMC0_DET/GPIO3_A1); also elsewhere on the board
U10_XIN: C54.1, R20.1, U10.68 (OSC_XIN), Y1.1
U10_XOUT: R19.1, U10.69 (OSC_XOUT)
U10_XOUT_R: C55.1, R19.2, R20.2, Y1.3
UART2_RX: U10.80 (JTAG_CPU_TMS_M1/GPIO1_B3); also elsewhere on the board
UART2_TX: U10.79 (JTAG_CPU_TCK_M1/GPIO1_B2); also elsewhere on the board
USB_DM: U10.26 (USB_DM); also elsewhere on the board
USB_DP: U10.27 (USB_DP); also elsewhere on the board
USB_VBUSDET: U10.25 (USB_VBUSDET); also elsewhere on the board
VCC_1V8: C36.1, C37.1, C38.1, FB1.1, FB2.1, R15.1, R25.1, U10.24 (SARADC_USB_AVDD1V8), U10.53 (DDR_PLL_AVDD1V8); also elsewhere on the board
VCC_1V8_CODEC: C41.1, C42.1, FB2.2, U10.31 (CODEC_AVDD1V8)
VCC_1V8_MIPI: C43.1, R15.2, U10.1 (MIPI_AVDD1V8); also elsewhere on the board
VCC_1V8_PLL: C39.1, C40.1, FB1.2, U10.70 (OSC_AVDD1V8), U10.96 (OTP_AVDD1V8)
VCC_3V3: C44.1, C45.1, C46.1, C47.1, C48.1, C49.1, C50.1, C51.1, FB3.1, R16.1, R21.1, U10.13 (GPIO4_VCC), U10.28 (USB_AVDD3V3), U10.43 (GPIO3_VCC), U10.61 (PMU_VCC3V3), U10.81 (GPIO1_VCC3V3), U10.88 (GPIO6_VCC), U10.108 (GPIO5_VCC); also elsewhere on the board
VCC_DDR: C32.1, C33.1, C34.1, C35.1, U10.49 (DDR_VDDQ_1), U10.50 (DDR_VDDQ_2), U10.56 (DDR_VDDQ_3); also elsewhere on the board
VCC_RTC: C53.1, R16.2, U10.19 (RTC_AVDD3V3)
VDD_0V9: C22.1, C23.1, C24.1, C25.1, C26.1, C27.1, C28.1, C29.1, C30.1, C31.1, U10.10 (DVDD_1), U10.51 (DVDD_2), U10.54 (DVDD_3), U10.55 (DVDD_4), U10.67 (PMU_DVDD0V9), U10.71 (OSC_PLL_DVDD), U10.82 (DVDD_5), U10.103 (DVDD_6), U10.115 (CPU_DVDD), U10.116 (DVDD_7); also elsewhere on the board
